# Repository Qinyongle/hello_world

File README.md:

# hello_world
learn how to use github
Now i am run here ,which is write a description
nanananan

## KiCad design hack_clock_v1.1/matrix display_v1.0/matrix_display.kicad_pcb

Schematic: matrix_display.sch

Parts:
C1, C2, C3, C4, C5, C6: 0.1uF; 0603_C
D1, D2, D3, D4, D5, D6: Matrix_LED
J1: Conn_01x05_Male; PinHeader_1x05_P2.00mm_Vertical
R1, R2, R3, R4, R5, R6: 10K; 0603_R
U1, U2, U3, U4, U5, U6: MAX7219; SOIC-24W_7.5x15.4mm_P1.27mm

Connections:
+5V: C1.1, C2.1, C3.1, C4.1, C5.1, C6.1, J1.1, R1.2, R2.2, R3.2, R4.2, R5.2, R6.2, U1.19, U2.19, U3.19, U4.19, U5.19, U6.19
/1DIG0: D1.9, U1.2
/1DIG1: D1.14, U1.11
/1DIG2: D1.8, U1.6
/1DIG3: D1.12, U1.7
/1DIG4: D1.1, U1.3
/1DIG5: D1.7, U1.10
/1DIG6: D1.2, U1.5
/1DIG7: D1.5, U1.8
/1SEGA: D1.3, U1.14
/1SEGB: D1.4, U1.16
/1SEGC: D1.10, U1.20
/1SEGD: D1.6, U1.23
/1SEGDP: D1.13, U1.22
/1SEGE: D1.11, U1.21
/1SEGF: D1.15, U1.15
/1SEGG: D1.16, U1.17
/2DIG0: D2.9, U2.2
/2DIG1: D2.14, U2.11
/2DIG2: D2.8, U2.6
/2DIG3: D2.12, U2.7
/2DIG4: D2.1, U2.3
/2DIG5: D2.7, U2.10
/2DIG6: D2.2, U2.5
/2DIG7: D2.5, U2.8
/2SEGA: D2.3, U2.14
/2SEGB: D2.4, U2.16
/2SEGC: D2.10, U2.20
/2SEGD: D2.6, U2.23
/2SEGDP: D2.13, U2.22
/2SEGE: D2.11, U2.21
/2SEGF: D2.15, U2.15
/2SEGG: D2.16, U2.17
/3DIG0: D3.9, U3.2
/3DIG1: D3.14, U3.11
/3DIG2: D3.8, U3.6
/3DIG3: D3.12, U3.7
/3DIG4: D3.1, U3.3
/3DIG5: D3.7, U3.10
/3DIG6: D3.2, U3.5
/3DIG7: D3.5, U3.8
/3SEGA: D3.3, U3.14
/3SEGB: D3.4, U3.16
/3SEGC: D3.10, U3.20
/3SEGD: D3.6, U3.23
/3SEGDP: D3.13, U3.22
/3SEGE: D3.11, U3.21
/3SEGF: D3.15, U3.15
/3SEGG: D3.16, U3.17
/4DIG0: D4.9, U4.2
/4DIG1: D4.14, U4.11
/4DIG2: D4.8, U4.6
/4DIG3: D4.12, U4.7
/4DIG4: D4.1, U4.3
/4DIG5: D4.7, U4.10
/4DIG6: D4.2, U4.5
/4DIG7: D4.5, U4.8
/4SEGA: D4.3, U4.14
/4SEGB: D4.4, U4.16
/4SEGC: D4.10, U4.20
/4SEGD: D4.6, U4.23
/4SEGDP: D4.13, U4.22
/4SEGE: D4.11, U4.21
/4SEGF: D4.15, U4.15
/4SEGG: D4.16, U4.17
/5DIG0: D5.9, U5.2
/5DIG1: D5.14, U5.11
/5DIG2: D5.8, U5.6
/5DIG3: D5.12, U5.7
/5DIG4: D5.1, U5.3
/5DIG5: D5.7, U5.10
/5DIG6: D5.2, U5.5
/5DIG7: D5.5, U5.8
/5SEGA: D5.3, U5.14
/5SEGB: D5.4, U5.16
/5SEGC: D5.10, U5.20
/5SEGD: D5.6, U5.23
/5SEGDP: D5.13, U5.22
/5SEGE: D5.11, U5.21
/5SEGF: D5.15, U5.15
/5SEGG: D5.16, U5.17
/6DIG0: D6.9, U6.2
/6DIG1: D6.14, U6.11
/6DIG2: D6.8, U6.6
/6DIG3: D6.12, U6.7
/6DIG4: D6.1, U6.3
/6DIG5: D6.7, U6.10
/6DIG6: D6.2, U6.5
/6DIG7: D6.5, U6.8
/6DOUT: U6.24
/6SEGA: D6.3, U6.14
/6SEGB: D6.4, U6.16
/6SEGC: D6.10, U6.20
/6SEGD: D6.6, U6.23
/6SEGDP: D6.13, U6.22
/6SEGE: D6.11, U6.21
/6SEGF: D6.15, U6.15
/6SEGG: D6.16, U6.17
/CLK: J1.5, U1.13, U2.13, U3.13, U4.13, U5.13, U6.13
/CS: J1.4, U1.12, U2.12, U3.12, U4.12, U5.12, U6.12
/DIN: J1.3, U1.1
GND: C1.2, C2.2, C3.2, C4.2, C5.2, C6.2, J1.2, U1.4, U1.9, U2.4, U2.9, U3.4, U3.9, U4.4, U4.9, U5.4, U5.9, U6.4, U6.9
unnamed: R1.1, U1.18
unnamed: R2.1, U2.18
unnamed: R3.1, U3.18
unnamed: R4.1, U4.18
unnamed: R5.1, U5.18
unnamed: R6.1, U6.18
unnamed: U1.24, U2.1
unnamed: U2.24, U3.1
unnamed: U3.24, U4.1
unnamed: U4.24, U5.1
unnamed: U5.24, U6.1

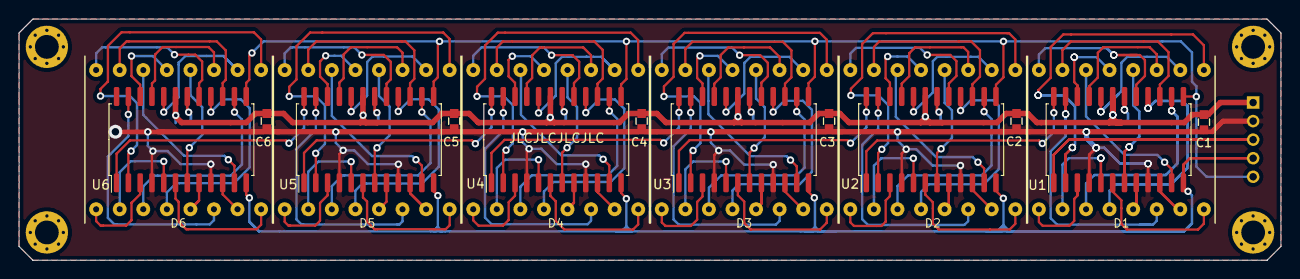
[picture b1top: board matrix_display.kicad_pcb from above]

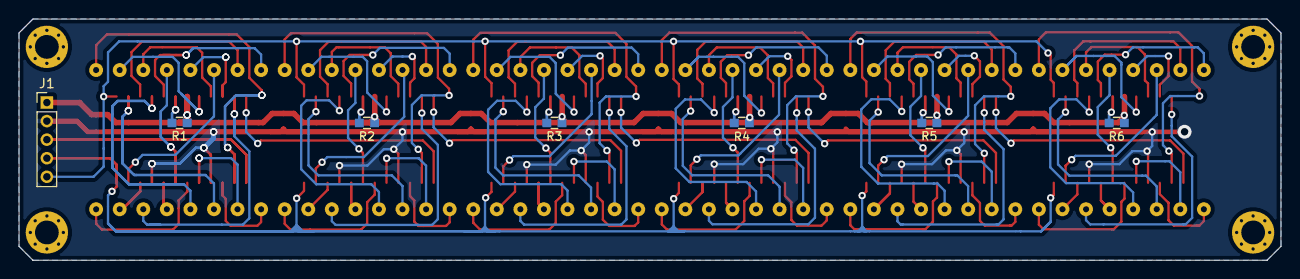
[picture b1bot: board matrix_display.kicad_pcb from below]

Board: 2 copper layers, 136.0 x 26.0 mm, 25 parts (7 on the bottom side), 112 nets.

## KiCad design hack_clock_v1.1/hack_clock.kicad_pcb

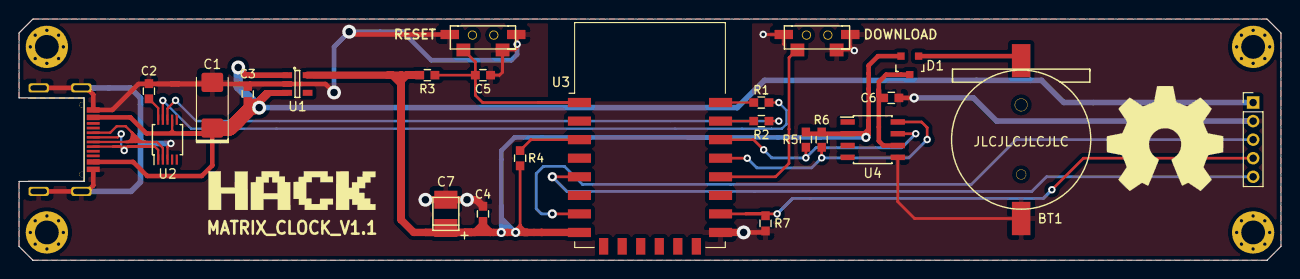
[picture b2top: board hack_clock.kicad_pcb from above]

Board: 2 copper layers, 136.0 x 26.0 mm, 26 parts (0 on the bottom side), 20 nets.

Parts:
BT1: BATTERY(M); CR1220-SMD
C1: 100uF; Tan-6032-20_AVX-F_NEW
C2, C5, C6: 0.1uF; 0603_C
C3, C4: 1uF; 0603_C
C7: 100uF; TantalC_SizeT_3528
D1: BAT54C; SOT-23
J1: Conn_01x05_Male; PinHeader_1x05_P2.00mm_Vertical
P3: USB_C_Plug_USB2.0; USB-Type-C
P665, P666: CON_1; CON1
R1, R2: RES(M); 0603_R
R3, R4, R5, R6, R7: 10K; 0603_R
SW1, SW2: switch; SWITCH_PUSH
U1: SPX3819; SOT23-5
U2: CH340E; TSSOP-10_3x3mm_P0.5mm
U3: ESP-12; ESP-12E
U4: DS3231MZ+; SOP-8

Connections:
+3V3: C4.2, C7.1, D1.2, R3.2, R4.2, R5.2, R6.2, U1.5, U3.8, U4.2
+5V: C1.1, C3.2, J1.1, P3.A4, U1.1, U1.3, U2.7
/CLK: J1.5, U3.5
/CS: J1.4, R7.2, U3.16
/DIN: J1.3, U3.7
/RXD: R1.2, U3.22
/SCL: R6.1, U3.19, U4.8
/SDA: R5.1, U3.20, U4.7
/TXD: R2.2, U3.21
/USB_D+: P3.A6, U2.1
/USB_D-: P3.A7, U2.2
GND: BT1.2, C1.2, C2.1, C3.1, C4.1, C5.1, C6.1, C7.2, J1.2, P3.A1, P3.S1, R7.1, SW1.1, SW2.1, U1.2, U2.3, U3.15, U4.5
unnamed: BT1.1, D1.1
unnamed: C2.2, U2.10
unnamed: C5.2, R3.1, SW1.2, U3.1
unnamed: C6.2, D1.3, U4.6
unnamed: R1.1, U2.9
unnamed: R2.1, U2.8
unnamed: R4.1, U3.3
unnamed: SW2.2, U3.18

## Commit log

2021-06-05 finish readme
    changes
2021-06-05 final-readme
    comcomcm
2021-06-20 first try
2021-06-20 second try
2021-06-20 dadd
2021-06-20 last
